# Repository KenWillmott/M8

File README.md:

# M8
## M8-standard
This KiCad project provides a starting template with which to design controller and peripheral boards that are compatible with the physical and electrical characteristics of the M8 bus system.

Please read the wiki for details:
https://github.com/KenWillmott/M8/wiki

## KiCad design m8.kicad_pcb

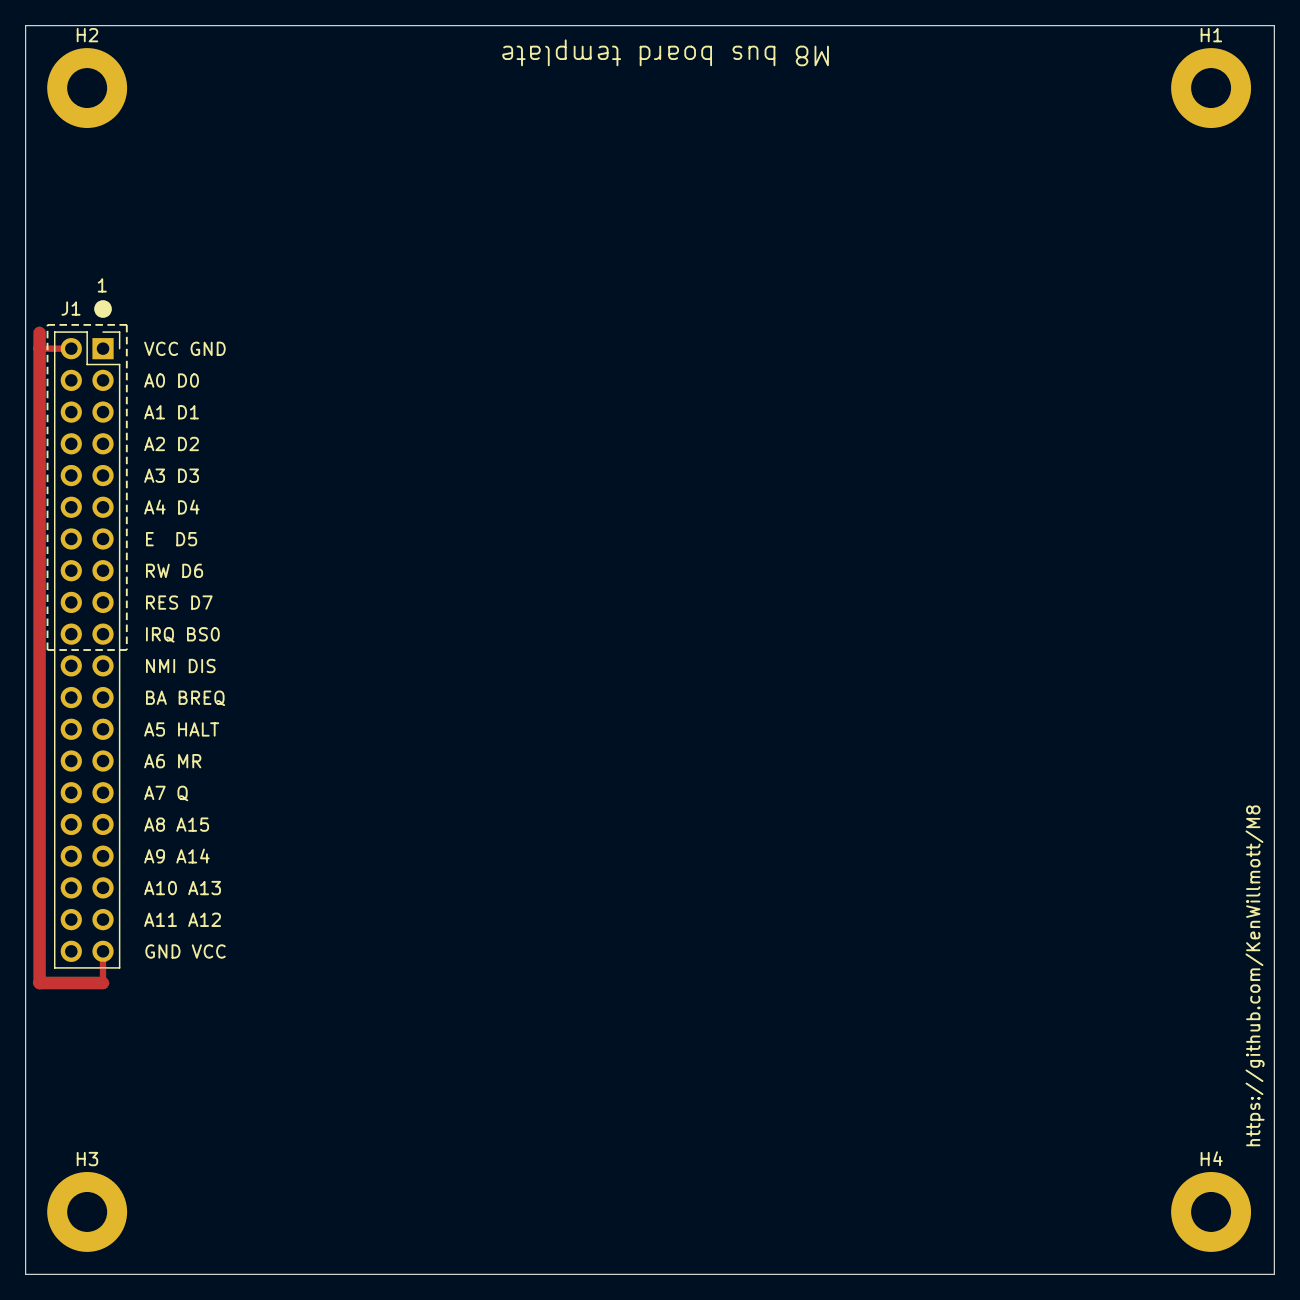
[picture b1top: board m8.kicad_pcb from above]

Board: 4 copper layers, 100.0 x 100.0 mm, 5 parts (0 on the bottom side), 2 nets.

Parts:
H1, H2, H3, H4: MountingHole_Pad; MountingHole_3.2mm_M3_Pad
J1: Conn_02x20_Odd_Even; PinSocket_2x20_P2.54mm_Vertical

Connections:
GND: H1.1, H2.1, H3.1, H4.1, J1.1, J1.40
VCC: J1.2, J1.39
